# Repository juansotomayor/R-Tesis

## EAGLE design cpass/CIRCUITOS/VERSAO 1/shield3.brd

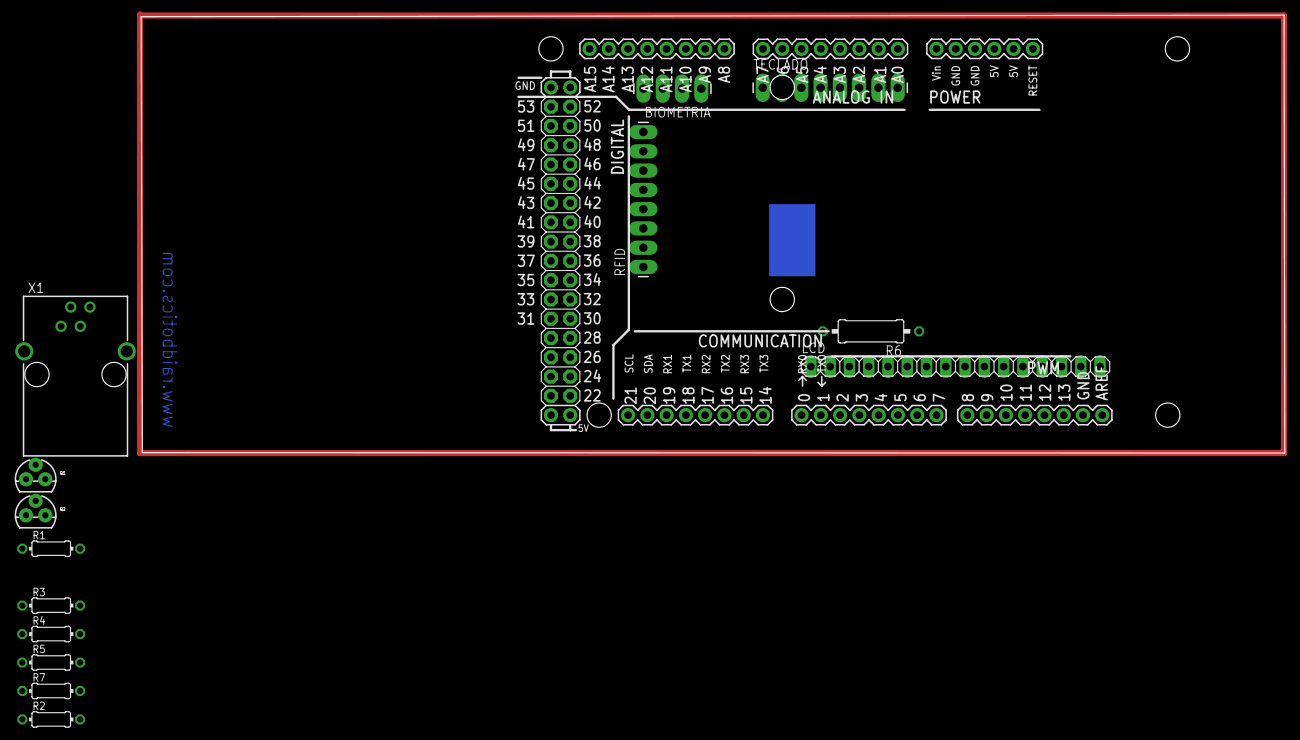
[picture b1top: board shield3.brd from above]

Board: 2 copper layers, 150.7 x 57.7 mm, 15 parts (0 on the bottom side), 31 nets.

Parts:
BIOMETRIA: 1X04_LONGPADS
LCD: 1X16
Q1, Q2: MOSFET-NCHANNEL2N7000; TO-92
R1, R2, R4, R5: 10k; 0204/7
R3, R7: 4.7k; 0204/7
R6: 0309/12
RFID: 1X08_LONGPADS
TECLADO: 1X08_LONGPADS
U1: ARDUINO-MEGAFULL; ARDUINO_MEGA
X1: XRJK-S-01-6-4-0-9M2

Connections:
5V: BIOMETRIA.2, LCD.2, R1.1, R3.1, R4.1, R7.1, U1.5V@0
7: LCD.4, U1.7
8: LCD.6, U1.8
9: LCD.11, U1.9
10: LCD.12, U1.10
11: LCD.13, U1.11
12: LCD.14, U1.12
13: LCD.15, U1.13
A0: TECLADO.8, U1.A0
A1: TECLADO.7, U1.A1
A2: TECLADO.6, U1.A2
A3: TECLADO.5, U1.A3
A4: TECLADO.4, U1.A4
A5: TECLADO.3, U1.A5
A6: TECLADO.2, U1.A6
A7: TECLADO.1, U1.A7
A14: BIOMETRIA.3, U1.A14
A15: BIOMETRIA.4, U1.A15
GND: R2.2, R5.2, U1.GND@4
GND1: RFID.6, U1.GND@0
unnamed: Q1.2, R2.1, R3.2
unnamed: Q2.2, R5.1, R7.2
unnamed: LCD.3, R6.2
unnamed: RFID.8, U1.3.3V
unnamed: BIOMETRIA.1, LCD.1, LCD.5, LCD.16, R6.1, U1.GND@2
unnamed: RFID.1, U1.48
RX1: Q1.3, R1.2, U1.19
SCK: RFID.2, U1.52
SI: RFID.3, U1.51
SO: RFID.4, U1.50
TX1: Q2.3, R4.2, U1.18

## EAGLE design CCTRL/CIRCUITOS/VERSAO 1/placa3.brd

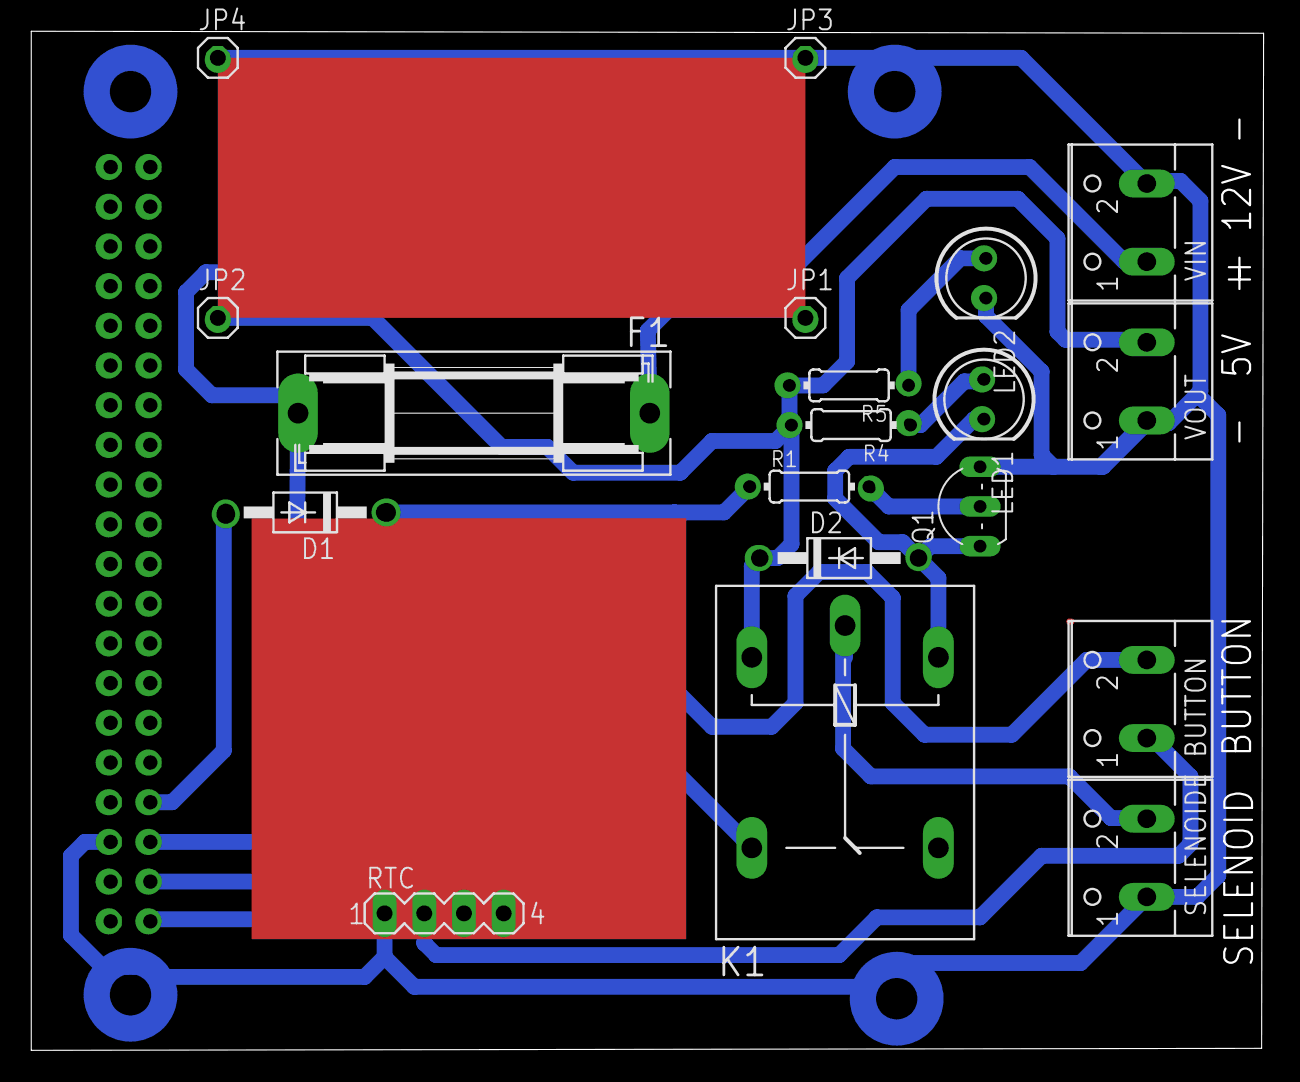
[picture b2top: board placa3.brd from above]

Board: 2 copper layers, 78.8 x 65.2 mm, 20 parts (1 on the bottom side), 14 nets.

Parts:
BUTTON: W237-102
D1, D2: 1N4004; DO41-10
F1: SH22,5
JP1, JP2, JP3, JP4: 1X01
K1: G5L; G5LE
LED1, LED2: LED5MM
Q1: BC548; TO92-EBC
R1: 0204/7
R4, R5: 220; 0204/7
RASPBERRY_PI_3: FE20-2
RTC: MA04-1
SELENOIDE: W237-102
VIN: W237-102
VOUT: +; W237-102

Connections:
3.3V: BUTTON.1, RASPBERRY_PI_3.1, RTC.2
5V: D2.C, JP2.1, K1.1, R4.2, R5.2, VOUT.2
GND: JP3.1, JP4.1, LED2.K, Q1.E, RASPBERRY_PI_3.6, RTC.1, SELENOIDE.1, VIN.2, VOUT.1
GPIO02: RASPBERRY_PI_3.3, RTC.3
GPIO03: RASPBERRY_PI_3.5, RTC.4
GPIO04: D1.A, RASPBERRY_PI_3.7
unnamed: BUTTON.2, D1.C, R1.1
unnamed: Q1.B, R1.2
unnamed: K1.P, SELENOIDE.2
unnamed: D2.A, K1.2, LED1.K, Q1.C
unnamed: LED2.A, R5.1
unnamed: F1.2, K1.S, VIN.1
unnamed: F1.1, JP1.1
unnamed: LED1.A, R4.1

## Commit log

2016-12-28 Archivos Bases
2016-12-29 Avance redaccion tesis
2016-12-30 Agrega los diagrama programacion arduino
2016-12-31 update cpass.js
    cambios operador if "RFID"
2016-12-31 Avance tesis

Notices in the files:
parts and their libraries:
SparkFun-Boards: Licensing: Creative Commons ShareAlike 4.0 International - https://creativecommons.org/licenses/by-sa/4.0
